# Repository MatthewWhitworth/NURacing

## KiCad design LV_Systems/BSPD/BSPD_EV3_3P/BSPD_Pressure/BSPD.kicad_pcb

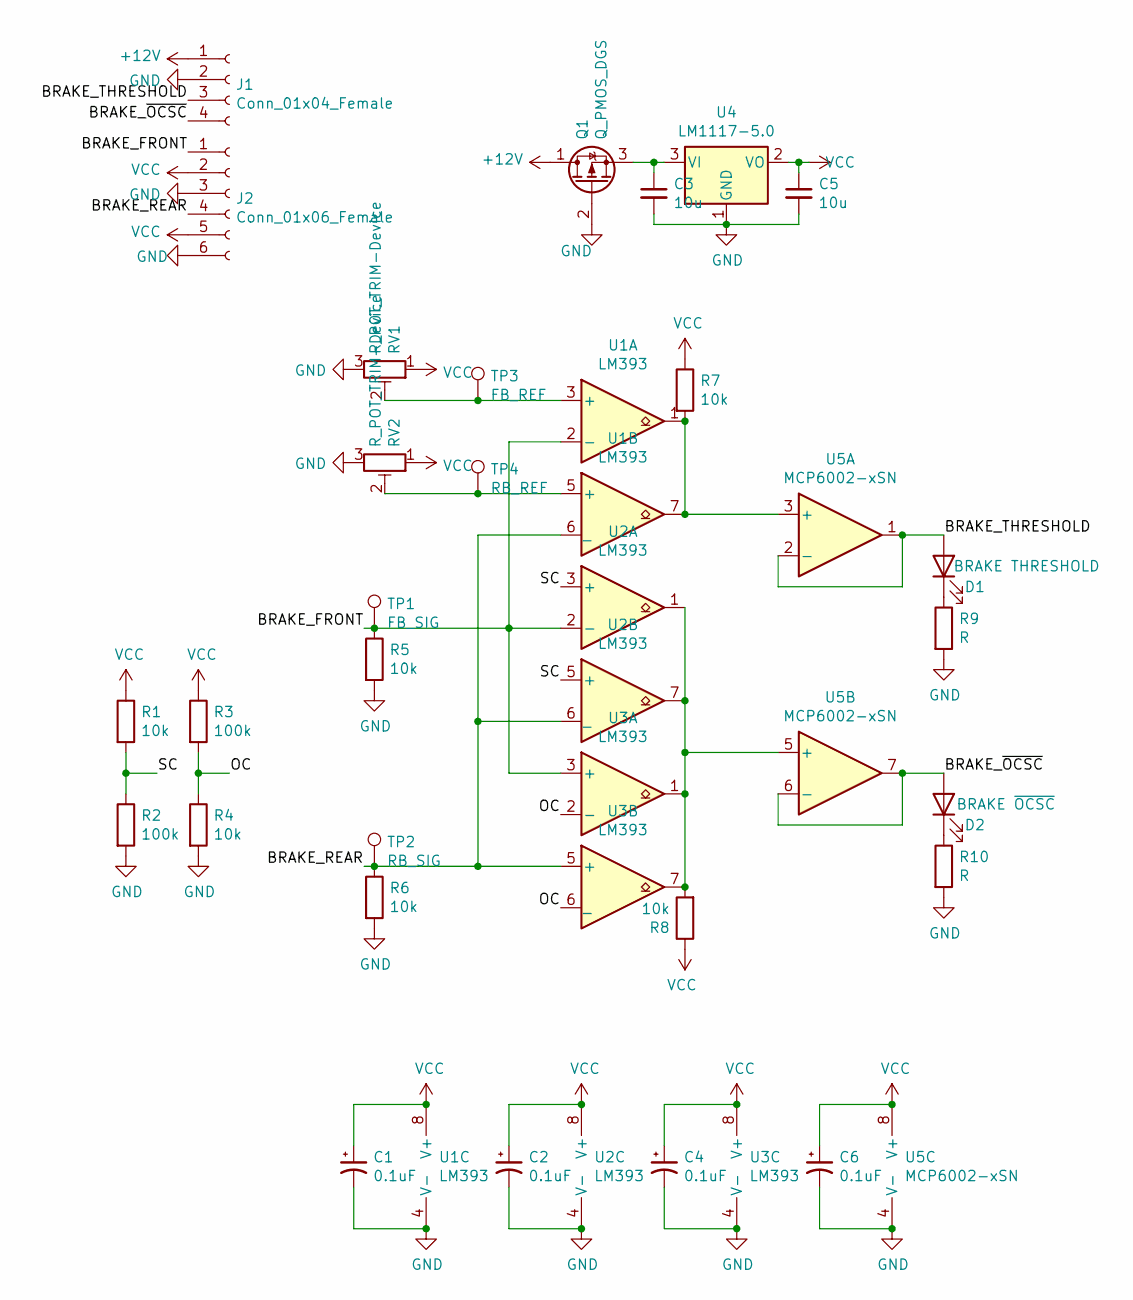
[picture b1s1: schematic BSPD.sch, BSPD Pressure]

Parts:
C1, C2, C4, C6: 0.1uF; C_0805_2012Metric
C3, C5: 10u; C_0805_2012Metric
D1: BRAKE THRESHOLD; LED_0805_2012Metric
D2: BRAKE ~OCSC; LED_0805_2012Metric
J1: Conn_01x04_Female; Molex_Micro-Fit_3.0_43045-0412_2x02_P3.00mm_Vertical
J2: Conn_01x06_Female; Molex_Micro-Fit_3.0_43045-0612_2x03_P3.00mm_Vertical
Q1: Q_PMOS_DGS; SOT-23
R1, R4, R5, R6, R7, R8: 10k; R_1206_3216Metric
R2, R3: 100k; R_1206_3216Metric
R9, R10: R; R_1206_3216Metric
RV1, RV2: R_POT_TRIM-Device; Potentiometer_Bourns_3296Y_Vertical
TP1: FB_SIG; TestPoint_Loop_D1.80mm_Drill1.0mm_Beaded
TP2: RB_SIG; TestPoint_Loop_D1.80mm_Drill1.0mm_Beaded
TP3: FB_REF; TestPoint_Loop_D1.80mm_Drill1.0mm_Beaded
TP4: RB_REF; TestPoint_Loop_D1.80mm_Drill1.0mm_Beaded
U1, U2, U3: LM393; SOIC-8_3.9x4.9mm_P1.27mm
U4: LM1117-5.0; SOT-223-3_TabPin2
U5: MCP6002-xSN; SOIC-8_3.9x4.9mm_P1.27mm

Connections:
+12V: J1.1, Q1.1 (D)
/BRAKE_FRONT: J2.1, R5.1, TP1.1, U1.2 (-), U2.2 (-), U3.3 (+)
/BRAKE_REAR: J2.4, R6.1, TP2.1, U1.6 (_), U2.6 (_), U3.5 (+)
/BRAKE_THRESHOLD: D1.2 (A), J1.3, U5.1, U5.2 (-)
/BRAKE_~OCSC: D2.2 (A), J1.4, U5.6 (-), U5.7
/OC: R3.2, R4.1, U3.2 (-), U3.6 (_)
/SC: R1.2, R2.1, U2.3 (+), U2.5 (+)
GND: C1.2, C2.2, C3.2, C4.2, C5.2, C6.2, J1.2, J2.3, J2.6, Q1.2 (G), R2.2, R4.2, R5.2, R6.2, R9.2, R10.2, RV1.3, RV2.3, U1.4 (V-), U2.4 (V-), U3.4 (V-), U4.1 (GND), U5.4 (V-)
unnamed: C3.1, Q1.3 (S), U4.3 (VI)
unnamed: D1.1 (K), R9.1
unnamed: D2.1 (K), R10.1
unnamed: R7.2, U1.1, U1.7, U5.3 (+)
unnamed: R8.2, U2.1, U2.7, U3.1, U3.7, U5.5 (+)
unnamed: RV1.2, TP3.1, U1.3 (+)
unnamed: RV2.2, TP4.1, U1.5 (+)
VCC: C1.1, C2.1, C4.1, C5.1, C6.1, J2.2, J2.5, R1.1, R3.1, R7.1, R8.1, RV1.1, RV2.1, U1.8 (V+), U2.8 (V+), U3.8 (V+), U4.2 (VO), U5.8 (V+)

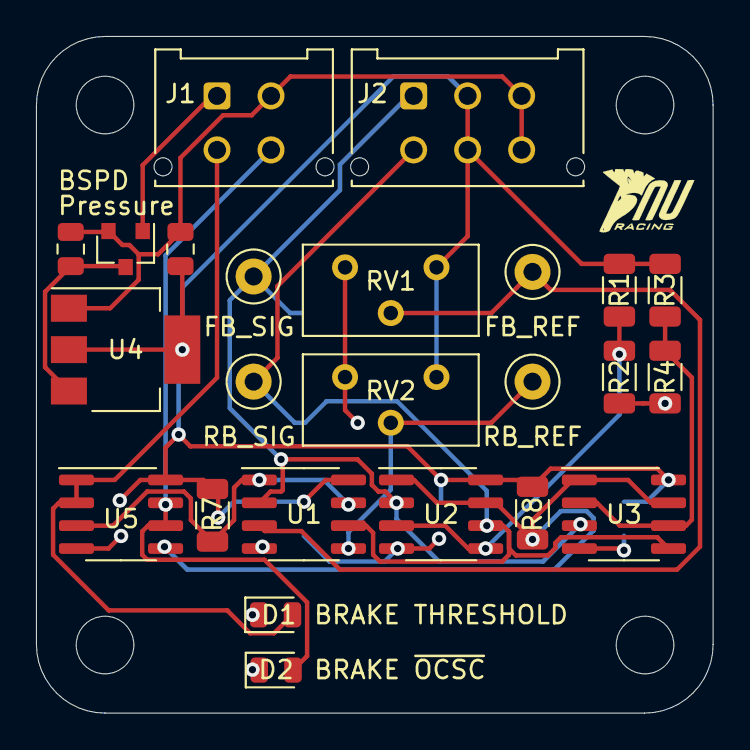
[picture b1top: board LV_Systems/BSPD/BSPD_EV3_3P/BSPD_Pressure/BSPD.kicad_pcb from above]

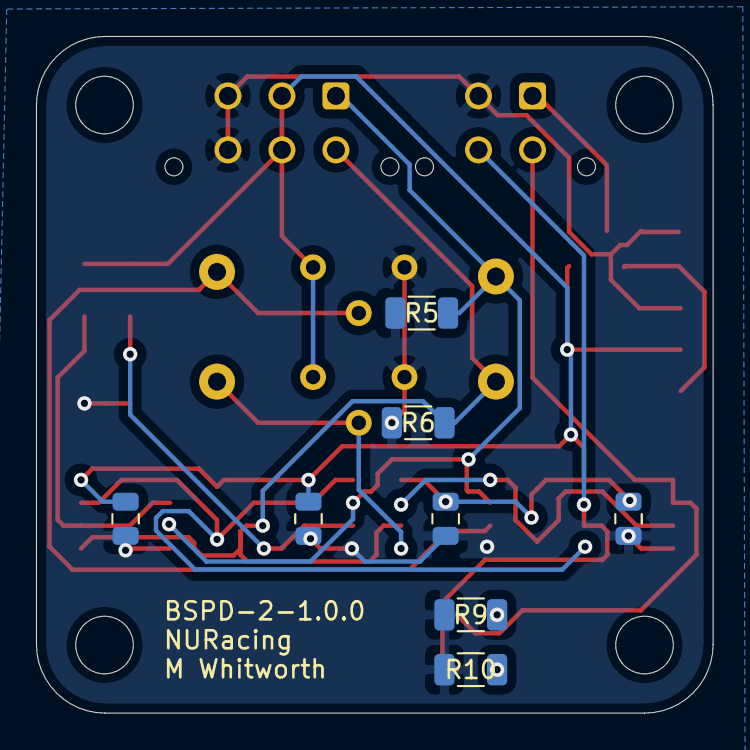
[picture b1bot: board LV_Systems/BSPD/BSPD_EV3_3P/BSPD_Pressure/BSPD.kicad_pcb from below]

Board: 2 copper layers, 37.6 x 37.6 mm, 32 parts (8 on the bottom side), 16 nets.

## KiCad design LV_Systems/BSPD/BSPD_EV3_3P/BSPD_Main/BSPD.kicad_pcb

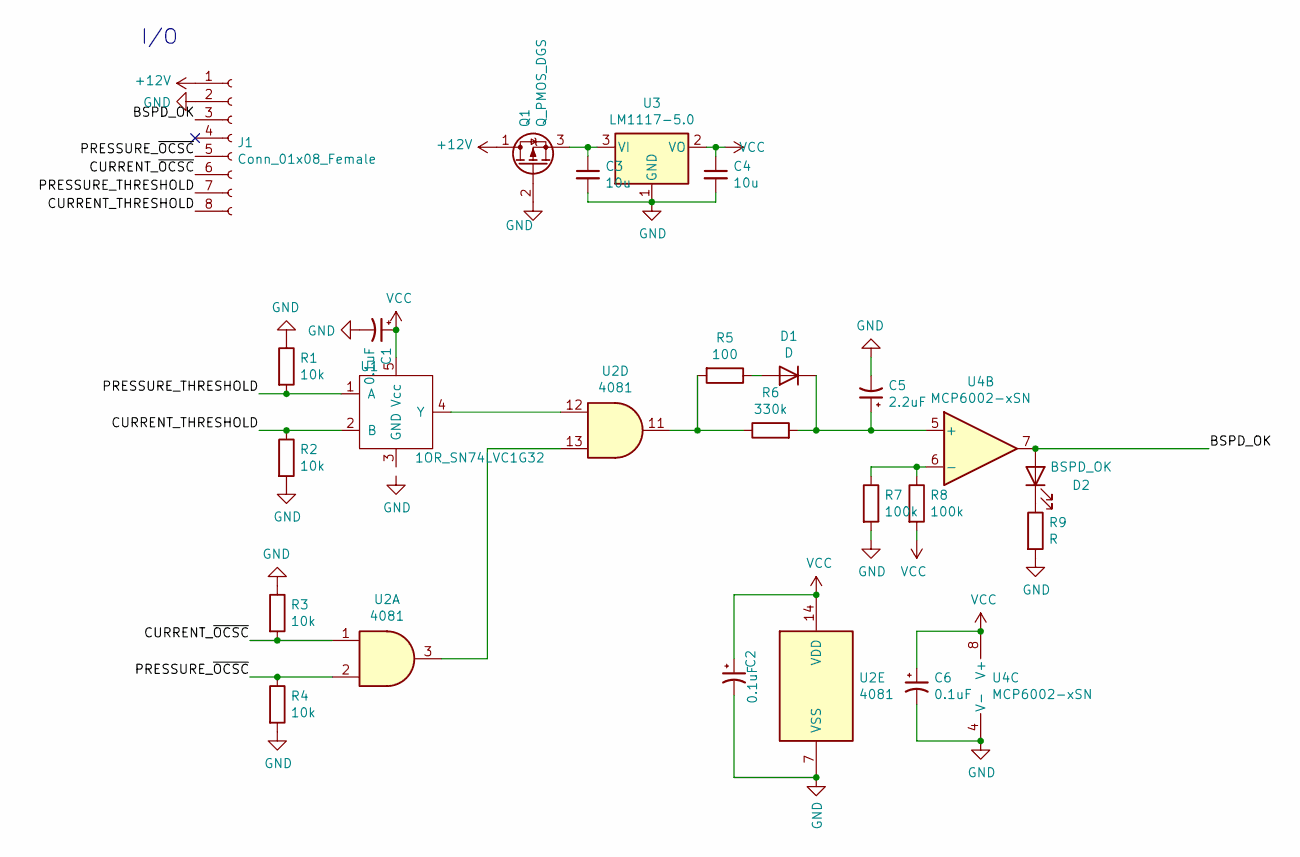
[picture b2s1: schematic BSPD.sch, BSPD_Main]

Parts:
C1, C2, C6: 0.1uF; C_0805_2012Metric
C3, C4: 10u; C_0805_2012Metric
C5: 2.2uF; C_0805_2012Metric
D1: D; D_SMA_Handsoldering
D2: BSPD_OK; LED_0805_2012Metric
J1: Conn_01x08_Female; Molex_Micro-Fit_3.0_43045-0812_2x04_P3.00mm_Vertical
Q1: Q_PMOS_DGS; SOT-23
R1, R2, R3, R4: 10k; R_1206_3216Metric
R5: 100; R_1206_3216Metric
R6: 330k; R_1206_3216Metric
R7, R8: 100k; R_1206_3216Metric
R9: R; R_1206_3216Metric
U1: 1OR_SN74LVC1G32; SOT-23-5_HandSoldering
U2: 4081; SOIC-14_3.9x8.7mm_P1.27mm
U3: LM1117-5.0; SOT-223-3_TabPin2
U4: MCP6002-xSN; SOIC-8_3.9x4.9mm_P1.27mm

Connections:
+12V: J1.1, Q1.1 (D)
/BSPD_OK: D2.2 (A), J1.3, U4.7
/CURRENT_THRESHOLD: J1.8, R2.1, U1.2 (B)
/CURRENT_~OCSC: J1.6, R3.2, U2.1
/PRESSURE_THRESHOLD: J1.7, R1.2, U1.1 (A)
/PRESSURE_~OCSC: J1.5, R4.1, U2.2
GND: C1.2, C2.2, C3.2, C4.2, C5.2, C6.2, J1.2, Q1.2 (G), R1.1, R2.2, R3.1, R4.2, R7.2, R9.2, U2.7 (VSS), U3.1 (GND), U4.4 (V-)
unnamed: C3.1, Q1.3 (S), U3.3 (VI)
unnamed: C5.1, D1.1 (K), R6.2, U4.5 (+)
unnamed: D1.2 (A), R5.1
unnamed: D2.1 (K), R9.1
unnamed: R5.2, R6.1, U2.11
unnamed: R7.1, R8.1, U4.6 (-)
unnamed: U1.4 (Y), U2.12
unnamed: U2.3, U2.13
VCC: C1.1, C2.1, C4.1, C6.1, R8.2, U1.5 (Vcc), U2.14 (VDD), U3.2 (VO), U4.8 (V+)

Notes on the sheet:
I/O

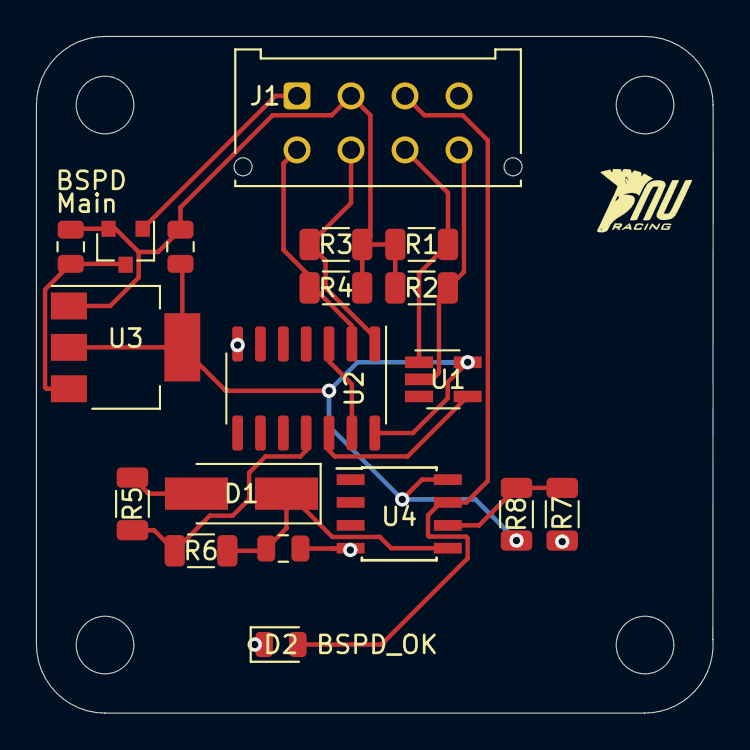
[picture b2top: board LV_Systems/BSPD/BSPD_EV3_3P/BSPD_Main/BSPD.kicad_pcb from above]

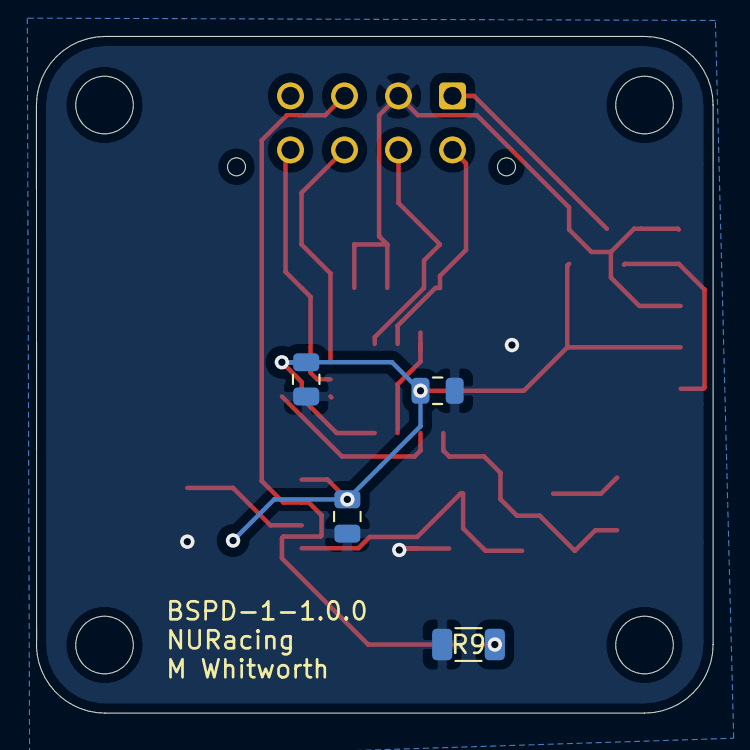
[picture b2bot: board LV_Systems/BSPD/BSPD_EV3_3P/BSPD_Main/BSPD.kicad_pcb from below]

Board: 2 copper layers, 37.6 x 37.6 mm, 23 parts (4 on the bottom side), 16 nets.

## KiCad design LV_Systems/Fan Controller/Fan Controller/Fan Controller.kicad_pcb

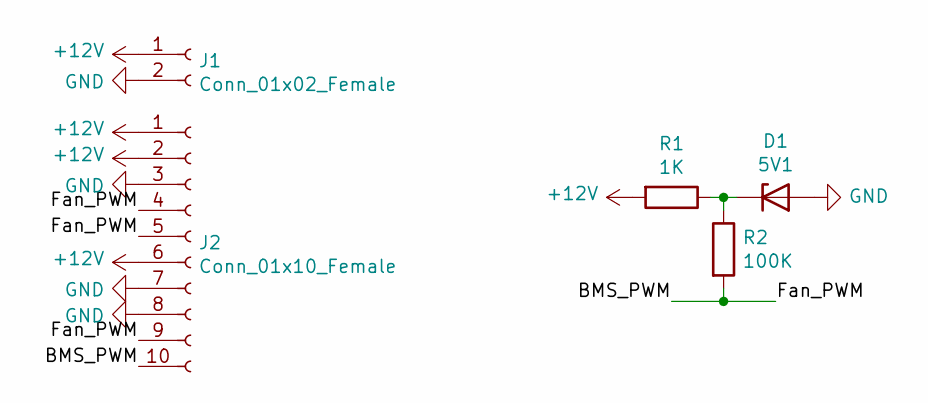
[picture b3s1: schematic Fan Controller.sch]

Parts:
D1: 5V1; SOT-23
J1: Conn_01x02_Female; Molex_Mini-Fit_Sr_42819-22XX_1x02_P10.00mm_Vertical
J2: Conn_01x10_Female; Molex_Micro-Fit_3.0_43045-1000_2x05_P3.00mm_Horizontal
R1: 1K; R_1206_3216Metric
R2: 100K; R_1206_3216Metric

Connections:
+12V: J1.1, J2.1, J2.2, J2.6, R1.2
/BMS_PWM: J2.4, J2.5, J2.9, J2.10, R2.2
GND: D1.2 (A), J1.2, J2.3, J2.7, J2.8
unnamed: D1.1 (K), R1.1, R2.1

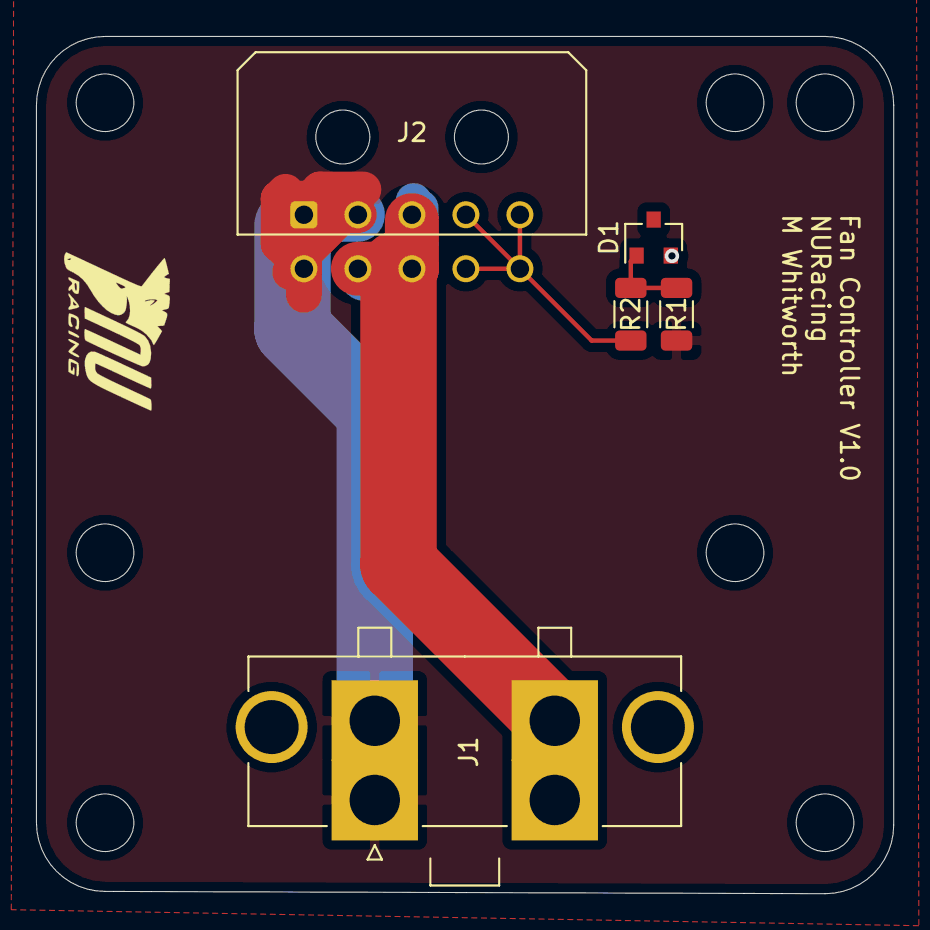
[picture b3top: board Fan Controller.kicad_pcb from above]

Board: 2 copper layers, 47.6 x 47.6 mm, 5 parts (0 on the bottom side), 4 nets.

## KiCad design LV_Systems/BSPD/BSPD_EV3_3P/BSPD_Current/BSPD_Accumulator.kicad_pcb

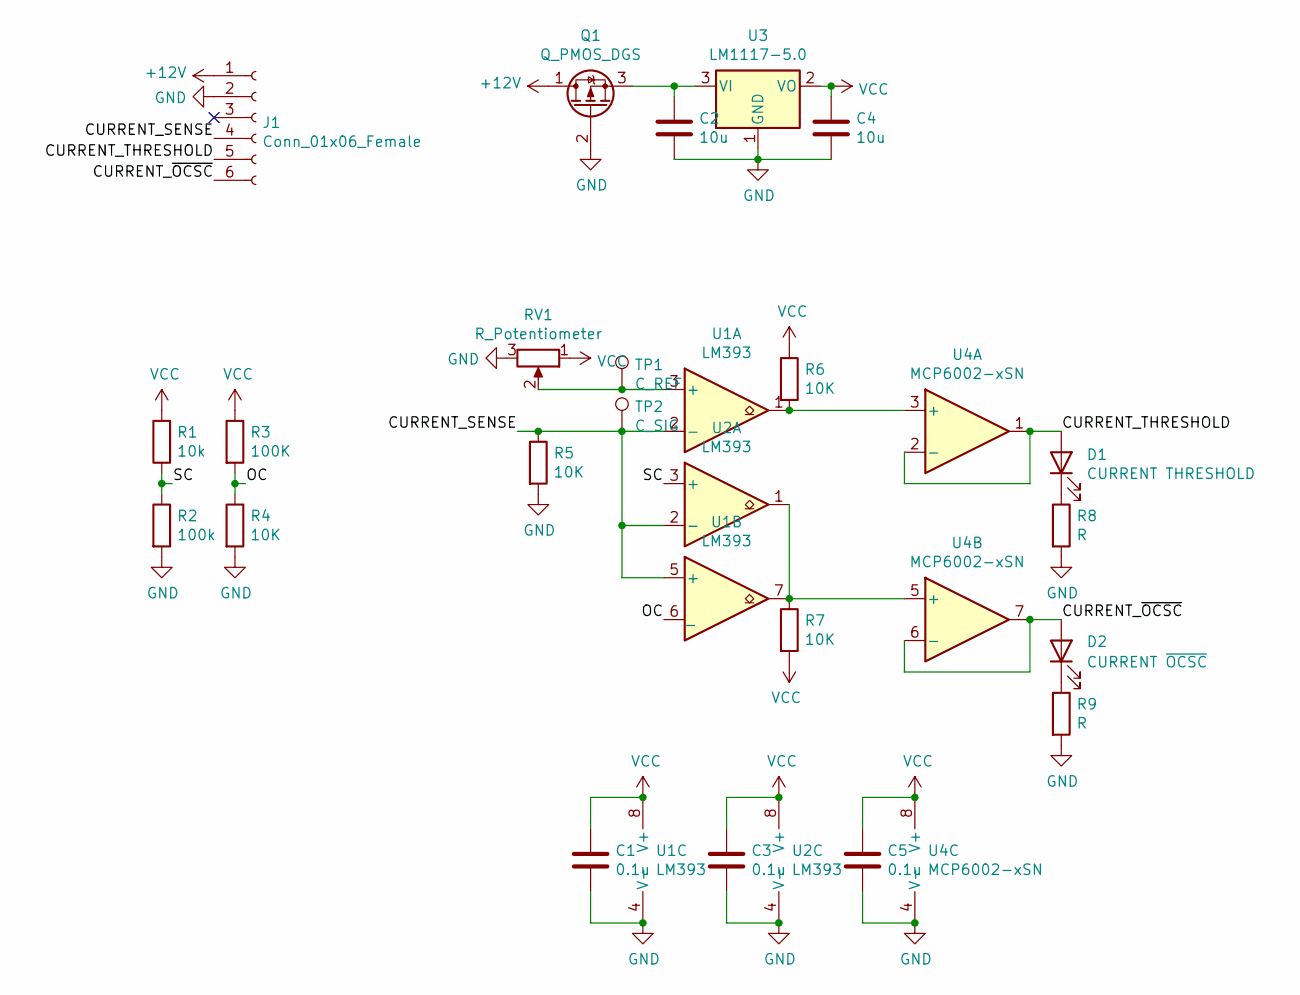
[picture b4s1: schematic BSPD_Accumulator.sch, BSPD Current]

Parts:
C1, C3, C5: 0.1u; C_0805_2012Metric
C2, C4: 10u; C_0805_2012Metric
D1: CURRENT THRESHOLD; LED_0805_2012Metric
D2: CURRENT ~OCSC; LED_0805_2012Metric
J1: Conn_01x06_Female; Molex_Micro-Fit_3.0_43045-0612_2x03_P3.00mm_Vertical
Q1: Q_PMOS_DGS; SOT-23
R1: 10k; R_1206_3216Metric
R2: 100k; R_1206_3216Metric
R3: 100K; R_1206_3216Metric
R4, R5, R6, R7: 10K; R_1206_3216Metric
R8, R9: R; R_1206_3216Metric
RV1: R_Potentiometer; Potentiometer_Bourns_3296Y_Vertical
TP1: C_REF; TestPoint_Loop_D1.80mm_Drill1.0mm_Beaded
TP2: C_SIG; TestPoint_Loop_D1.80mm_Drill1.0mm_Beaded
U1, U2: LM393; SOIC-8_3.9x4.9mm_P1.27mm
U3: LM1117-5.0; SOT-223-3_TabPin2
U4: MCP6002-xSN; SOIC-8_3.9x4.9mm_P1.27mm

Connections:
+12V: J1.1, Q1.1 (D)
/CURRENT_SENSE: J1.4, R5.1, TP2.1, U1.2 (-), U1.5 (+), U2.2 (-)
/CURRENT_THRESHOLD: D1.2 (A), J1.5, U4.1, U4.2 (-)
/CURRENT_~OCSC: D2.2 (A), J1.6, U4.6 (-), U4.7
/OC: R3.2, R4.1, U1.6 (_)
/SC: R1.1, R2.1, U2.3 (+)
GND: C1.2, C2.2, C3.2, C4.2, C5.2, J1.2, Q1.2 (G), R2.2, R4.2, R5.2, R8.2, R9.2, RV1.3, U1.4 (V-), U2.4 (V-), U3.1 (GND), U4.4 (V-)
unnamed: C2.1, Q1.3 (S), U3.3 (VI)
unnamed: D1.1 (K), R8.1
unnamed: D2.1 (K), R9.1
unnamed: R6.2, U1.1, U4.3 (+)
unnamed: R7.1, U1.7, U2.1, U4.5 (+)
unnamed: RV1.2, TP1.1, U1.3 (+)
VCC: C1.1, C3.1, C4.1, C5.1, R1.2, R3.1, R6.1, R7.2, RV1.1, U1.8 (V+), U2.8 (V+), U3.2 (VO), U4.8 (V+)

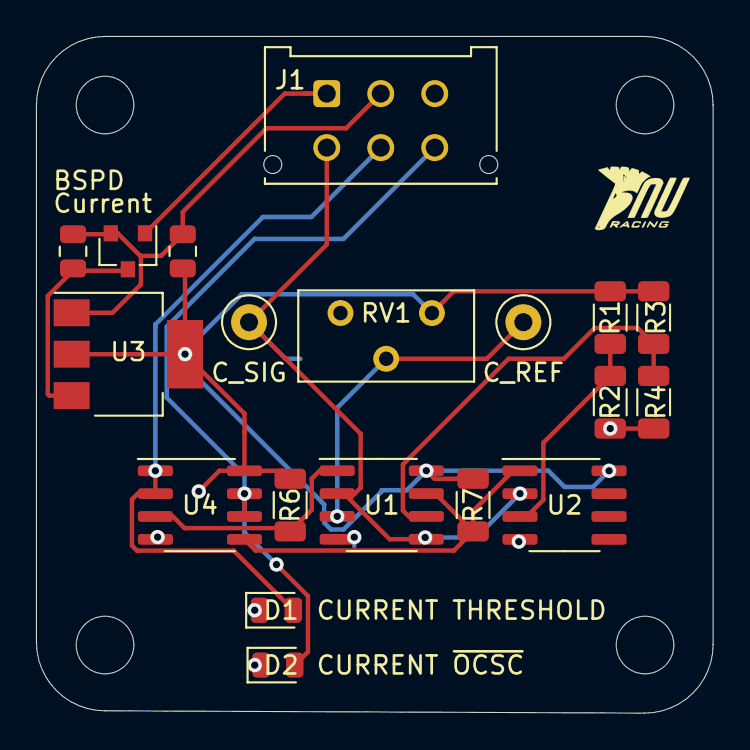
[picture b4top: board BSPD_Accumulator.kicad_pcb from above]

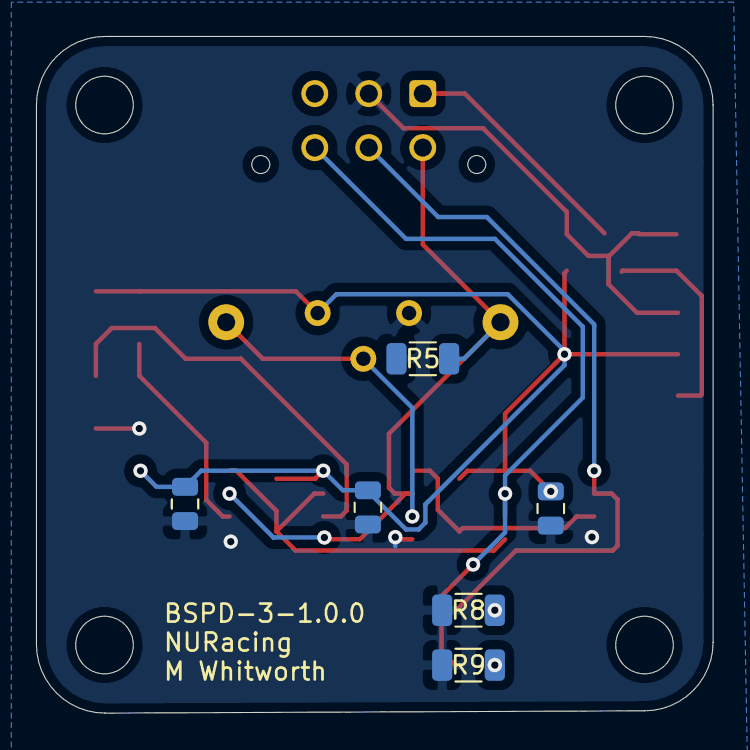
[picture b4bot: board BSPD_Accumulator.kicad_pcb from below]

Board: 2 copper layers, 37.6 x 37.6 mm, 25 parts (6 on the bottom side), 14 nets.

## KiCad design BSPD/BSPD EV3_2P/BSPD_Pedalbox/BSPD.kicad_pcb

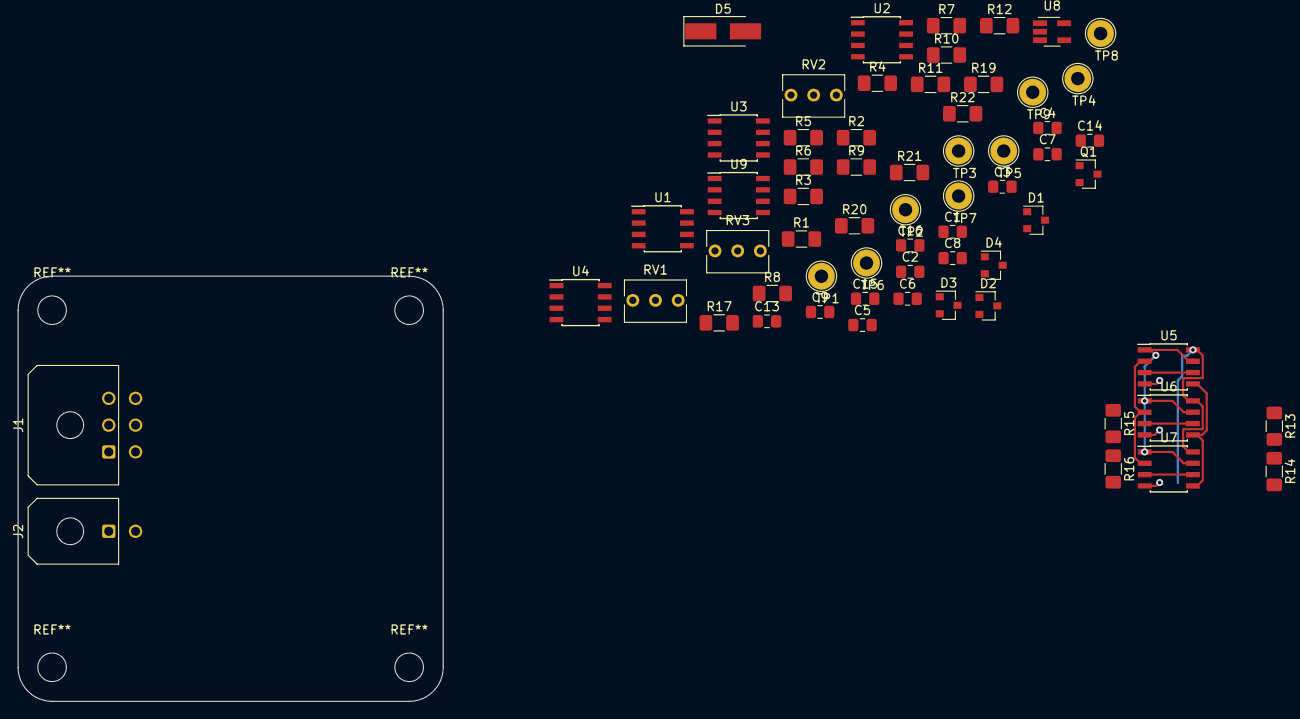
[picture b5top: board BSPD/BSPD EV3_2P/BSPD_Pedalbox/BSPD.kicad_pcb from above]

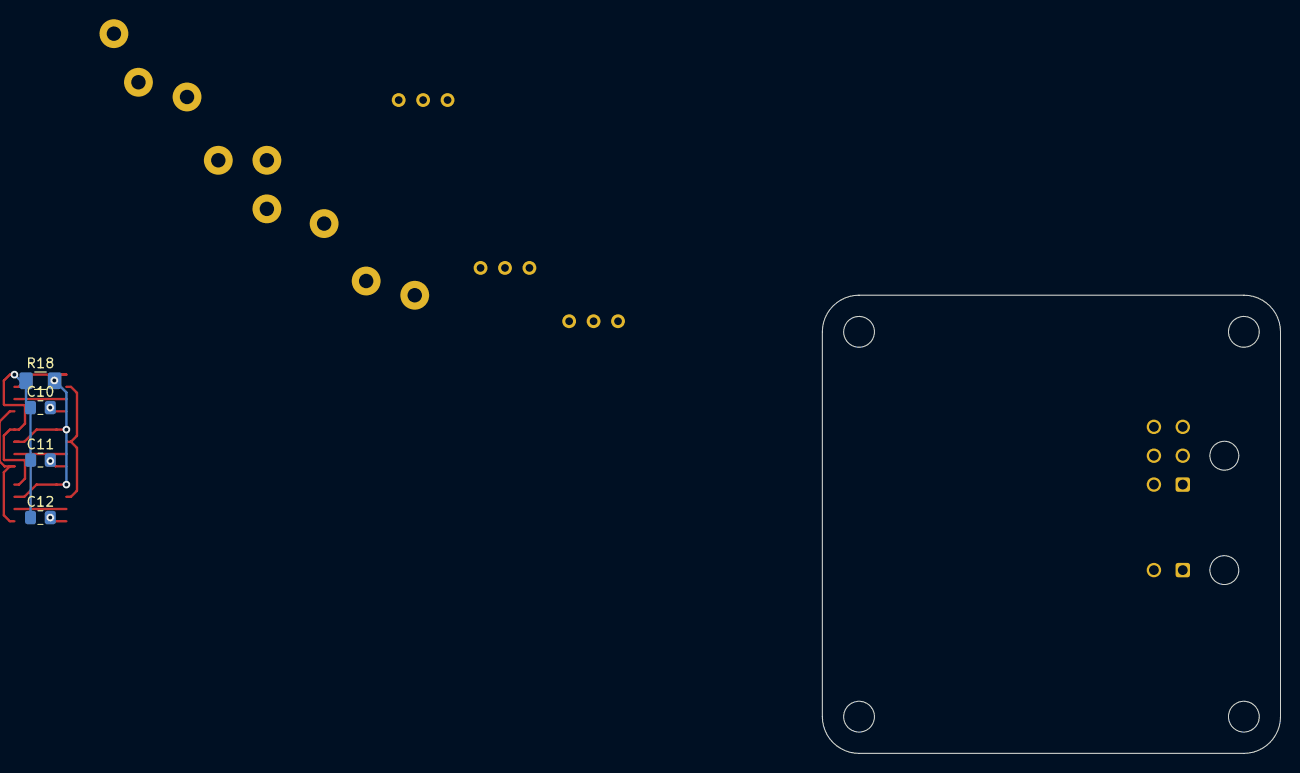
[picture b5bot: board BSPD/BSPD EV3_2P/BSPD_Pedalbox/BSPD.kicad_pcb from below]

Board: 2 copper layers, 47.6 x 47.6 mm, 67 parts (4 on the bottom side), 29 nets.

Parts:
C1, C2, C3: CP1_Small; C_0805_2012Metric_Pad1.15x1.40mm_HandSolder
C4, C5, C8: 0.1u; C_0805_2012Metric_Pad1.15x1.40mm_HandSolder
C6, C7, C9, C10, C11, C12, C13, C14, C15: 0.1uF; C_0805_2012Metric_Pad1.15x1.40mm_HandSolder
C16: 2.2uF; C_0805_2012Metric_Pad1.15x1.40mm_HandSolder
D1, D2, D3: D_Zener_Small; SOT-23
D4: D_Zener; SOT-23
D5: D; D_SMA_Handsoldering
J1: Conn_01x06_Female; Molex_Micro-Fit_3.0_43045-0600_2x03_P3.00mm_Horizontal
J2: Conn_01x02_Female; Molex_Micro-Fit_3.0_43045-0200_2x01_P3.00mm_Horizontal
Q1: Q_PMOS_DGS; SOT-23
R1, R2, R3, R4, R5, R6, R7, R8, R9, R12: R; R_1206_3216Metric_Pad1.42x1.75mm_HandSolder
R10, R11, R13, R16, R17, R18: 10k; R_1206_3216Metric_Pad1.42x1.75mm_HandSolder
R14, R15, R21, R22: 100k; R_1206_3216Metric_Pad1.42x1.75mm_HandSolder
R19: 100; R_1206_3216Metric_Pad1.42x1.75mm_HandSolder
R20: 330k; R_1206_3216Metric_Pad1.42x1.75mm_HandSolder
RV1, RV2, RV3: 10k; Potentiometer_Bourns_3266Y_Vertical
TP1, TP2, TP5: Ref; TestPoint_Loop_D2.54mm_Drill1.5mm_Beaded
TP3, TP4, TP6: Sig; TestPoint_Loop_D2.54mm_Drill1.5mm_Beaded
TP7: BrkFrnt; TestPoint_Loop_D2.54mm_Drill1.5mm_Beaded
TP8: BrkRear; TestPoint_Loop_D2.54mm_Drill1.5mm_Beaded
TP9: Current; TestPoint_Loop_D2.54mm_Drill1.5mm_Beaded
U1, U2, U3: LM311; SOIC-8_3.9x4.9mm_P1.27mm
U4: 74AUC2G08; SOIC-8_3.9x4.9mm_P1.27mm
U5, U6, U7: LM393; SOIC-8_3.9x4.9mm_P1.27mm
U8: 1OR_SN74LVC1G32; SOT-23-5_HandSoldering
U9: MCP6002-xSN; SOIC-8_3.9x4.9mm_P1.27mm

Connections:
+5V: J2.1, Q1.1
/BRK_FRNT: R8.1, R10.2, TP7.1, U1.7, U4.1
/BRK_REAR: R9.1, R11.1, TP8.1, U2.7, U4.2
/BRK_SIG: U4.7, U8.2
/Brk_Frnt_Inp: C1.1, C4.2, D1.1, R1.1, R4.1, TP3.1, U1.3, U6.3, U6.6
/Brk_Rear_Inp: C2.1, C5.2, D2.1, R2.1, R5.1, TP4.1, U2.3, U7.3, U7.6
/CRNT_SIG: R12.1, R17.2, TP9.1, U3.7, U8.1
/Crnt_Sig_Inp: C3.1, C8.2, D3.1, R3.1, R6.1, TP6.1, U3.3, U5.3, U5.6
/OC: R15.2, R16.1, U5.2, U6.2, U7.2
/Plausibility: U4.5, U8.4
/SC: R13.2, R14.1, U5.5, U6.5, U7.5
/~FLT_SIG: R19.2, R20.1, U4.3
/~OCSC: R18.2, U4.6, U5.1, U5.7, U6.1, U6.7, U7.1, U7.7
BSPD_Sig: J1.1, U9.1
GND: C1.2, C2.2, C3.2, C6.2, C7.2, C9.2, C10.2, C11.2, C12.2, C13.2, C14.2, C15.2, C16.2, D1.2, D2.2, D3.2, J1.5, J2.2, R4.2, R5.2, R6.2, R7.2, R14.2, R16.2, R21.2, RV1.3, RV2.3, RV3.3, U1.1, U1.4, U2.1, U2.4, U3.1, U3.4, U4.4, U5.4, U6.4, U7.4, U8.3, U9.4, U9.6
unnamed: C4.1, R8.2, RV1.2, TP1.1, U1.2
unnamed: C5.1, R9.2, RV2.2, TP2.1, U2.2
unnamed: C8.1, R12.2, RV3.2, TP5.1, U3.2
unnamed: C16.1, D5.1, R20.2, U9.3
unnamed: D4.2, Q1.2, R7.1
unnamed: D5.2, R19.1
unnamed: J1.2, R3.2
unnamed: J1.3, R2.2
unnamed: J1.4, R1.2
unnamed: R21.1, R22.1, U9.2
unnamed: U1.5, U1.6
unnamed: U2.5, U2.6
unnamed: U3.5, U3.6
VCC: C6.1, C7.1, C9.1, C10.1, C11.1, C12.1, C13.1, C14.1, C15.1, D4.1, J1.6, Q1.3, R10.1, R11.2, R13.1, R15.1, R17.1, R18.1, R22.2, RV1.1, RV2.1, RV3.1, U1.8, U2.8, U3.8, U4.8, U5.8, U6.8, U7.8, U8.5, U9.5, U9.8

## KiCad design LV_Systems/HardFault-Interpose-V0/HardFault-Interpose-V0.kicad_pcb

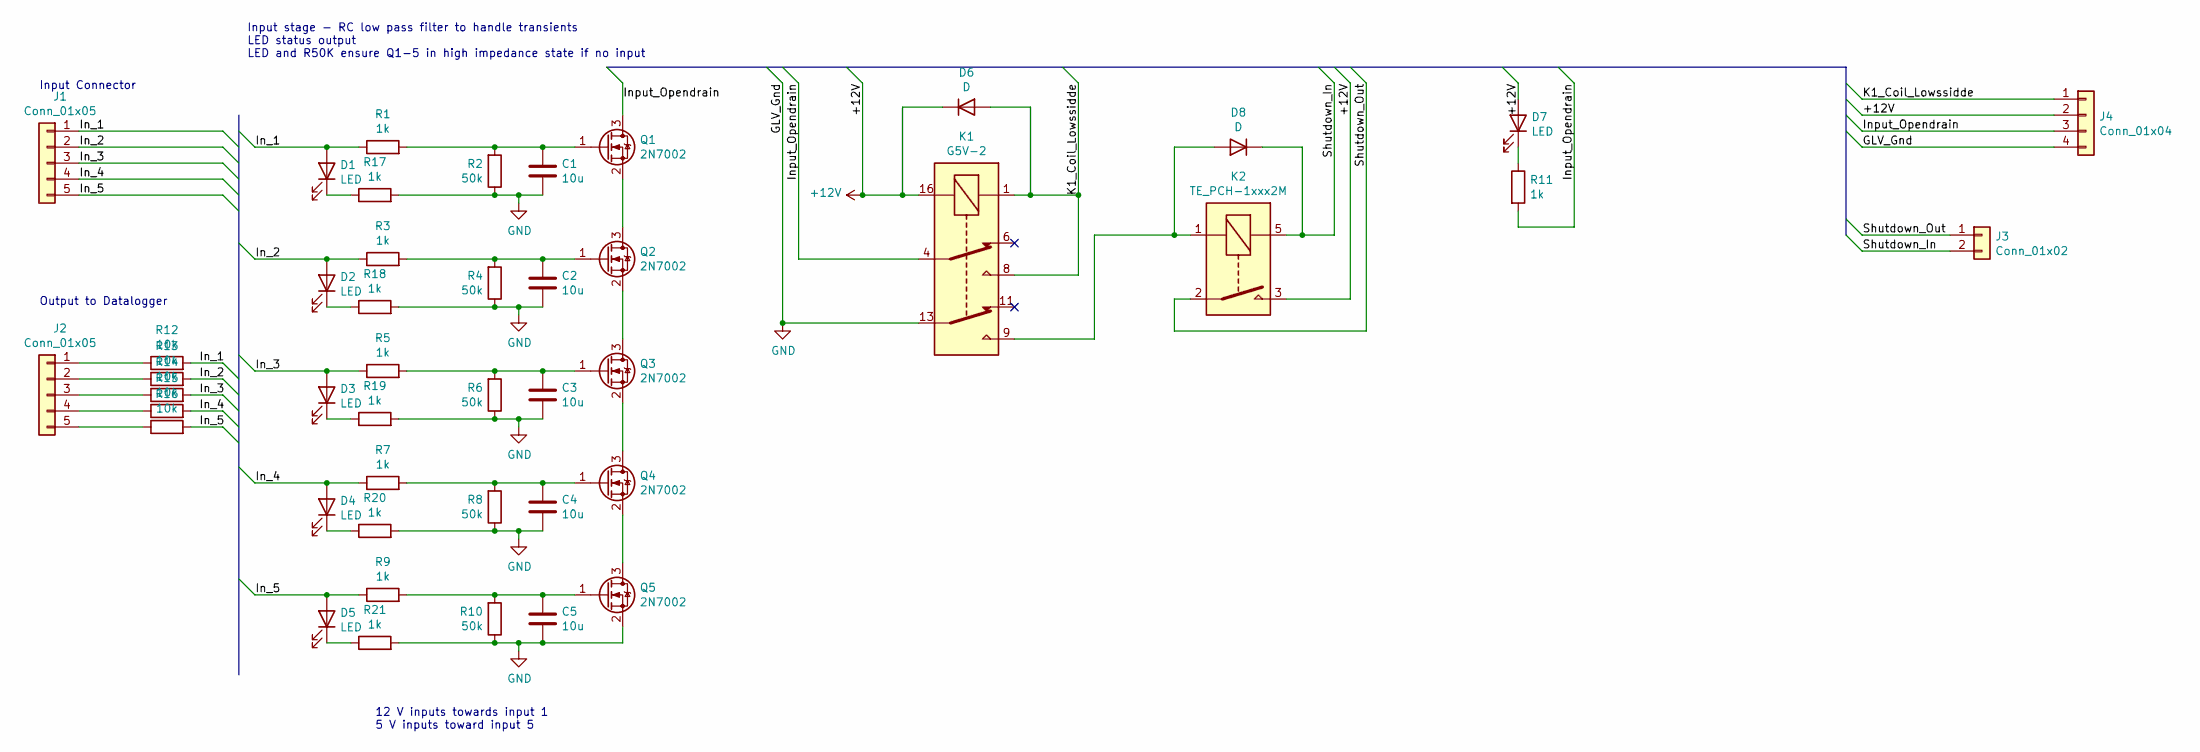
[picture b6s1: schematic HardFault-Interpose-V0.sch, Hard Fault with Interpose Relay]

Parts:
C1, C2, C3, C4, C5: 10u; C_0805_2012Metric_Pad1.15x1.40mm_HandSolder
D1, D2, D3, D4, D5, D7: LED; LED_0805_2012Metric_Castellated
D6, D8: D; D_SMA
J1, J2: Conn_01x05; Molex_Micro-Fit_3.0_43650-0515_1x05_P3.00mm_Vertical
J3: Conn_01x02; Molex-Mini-Fit-Jr-2-pin-P4.2mm-RowP4.2mm
J4: Conn_01x04; Molex-Mini-Fit-Jr-4-pin-P4.2mm-RowP4.2mm
K1: G5V-2; Relay_DPDT_Omron_G5V-2
K2: TE_PCH-1xxx2M; Relay_SPST_TE_PCH-1xxx2M
Q1, Q2, Q3, Q4, Q5: 2N7002; SOT-23
R1, R3, R5, R7, R9, R11, R17, R18, R19, R20, R21: 1k; R_1206_3216Metric_Pad1.42x1.75mm_HandSolder
R2, R4, R6, R8, R10: 50k; R_1206_3216Metric_Pad1.42x1.75mm_HandSolder
R12, R13, R14, R15, R16: 10k; R_1206_3216Metric_Pad1.42x1.75mm_HandSolder

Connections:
+12V: D6.1 (K), D7.2 (A), J4.2, K1.16, K2.3
/In_1: D1.2 (A), J1.1, R1.1, R12.2
/In_2: D2.2 (A), J1.2, R3.1, R13.2
/In_3: D3.2 (A), J1.3, R5.1, R14.2
/In_4: D4.2 (A), J1.4, R7.1, R15.2
/In_5: D5.2 (A), J1.5, R9.1, R16.2
/Input_Opendrain: J4.3, K1.4, Q1.3 (D), R11.2
/K1_Coil_Lowssidde: D6.2 (A), J4.1, K1.1, K1.8
/Shutdown_In: D8.1 (K), J3.2, K2.5
/Shutdown_Out: J3.1, K2.2
GND: C1.2, C2.2, C3.2, C4.2, C5.2, J4.4, K1.13, Q5.2 (S), R2.1, R4.1, R6.1, R8.1, R10.1, R17.2, R18.2, R19.2, R20.2, R21.2
unnamed: C1.1, Q1.1 (G), R1.2, R2.2
unnamed: C2.1, Q2.1 (G), R3.2, R4.2
unnamed: C3.1, Q3.1 (G), R5.2, R6.2
unnamed: C4.1, Q4.1 (G), R7.2, R8.2
unnamed: C5.1, Q5.1 (G), R9.2, R10.2
unnamed: D1.1 (K), R17.1
unnamed: D2.1 (K), R18.1
unnamed: D3.1 (K), R19.1
unnamed: D4.1 (K), R20.1
unnamed: D5.1 (K), R21.1
unnamed: D7.1 (K), R11.1
unnamed: D8.2 (A), K1.9, K2.1
unnamed: J2.1, R12.1
unnamed: J2.2, R13.1
unnamed: J2.3, R14.1
unnamed: J2.4, R15.1
unnamed: J2.5, R16.1
unnamed: Q1.2 (S), Q2.3 (D)
unnamed: Q2.2 (S), Q3.3 (D)
unnamed: Q3.2 (S), Q4.3 (D)
unnamed: Q4.2 (S), Q5.3 (D)

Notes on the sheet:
Input stage - RC low pass filter to handle transients LED status output LED and R50K ensure Q1-5 in high impedance state if no input
Input Connector
Output to Datalogger
12 V inputs towards input 1 5 V inputs toward input 5

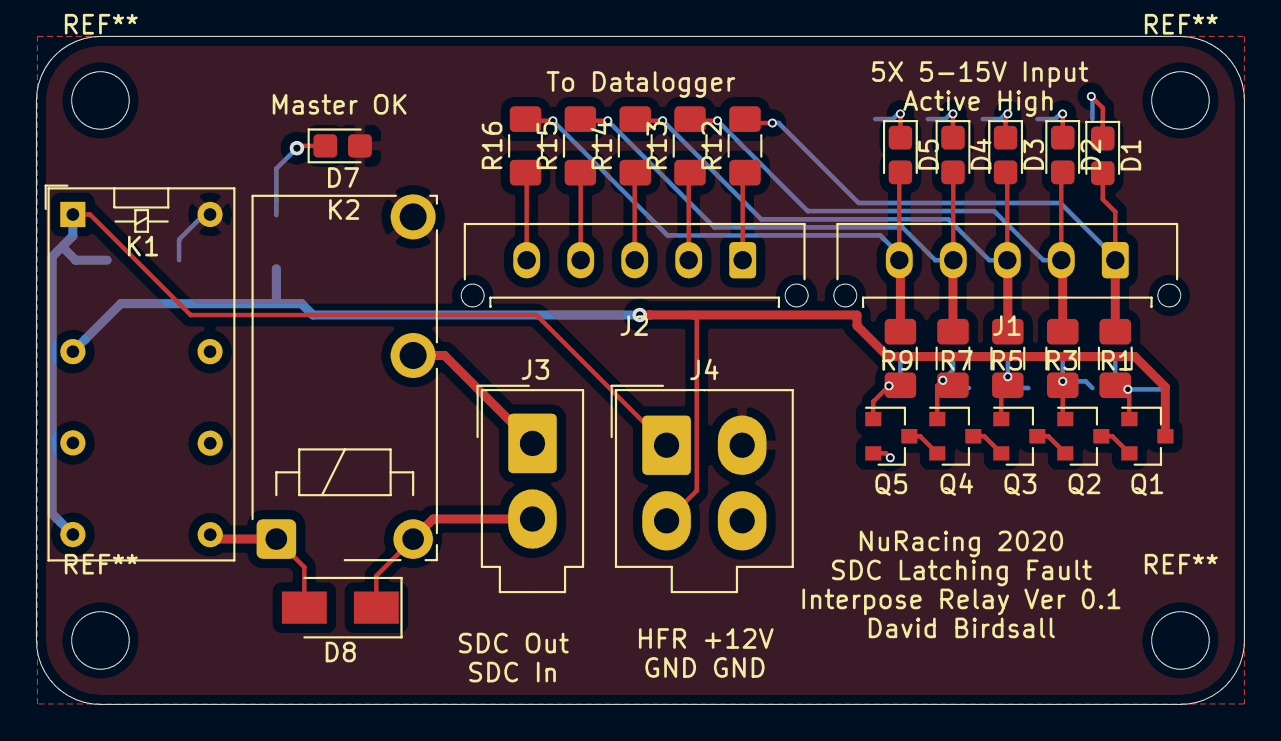
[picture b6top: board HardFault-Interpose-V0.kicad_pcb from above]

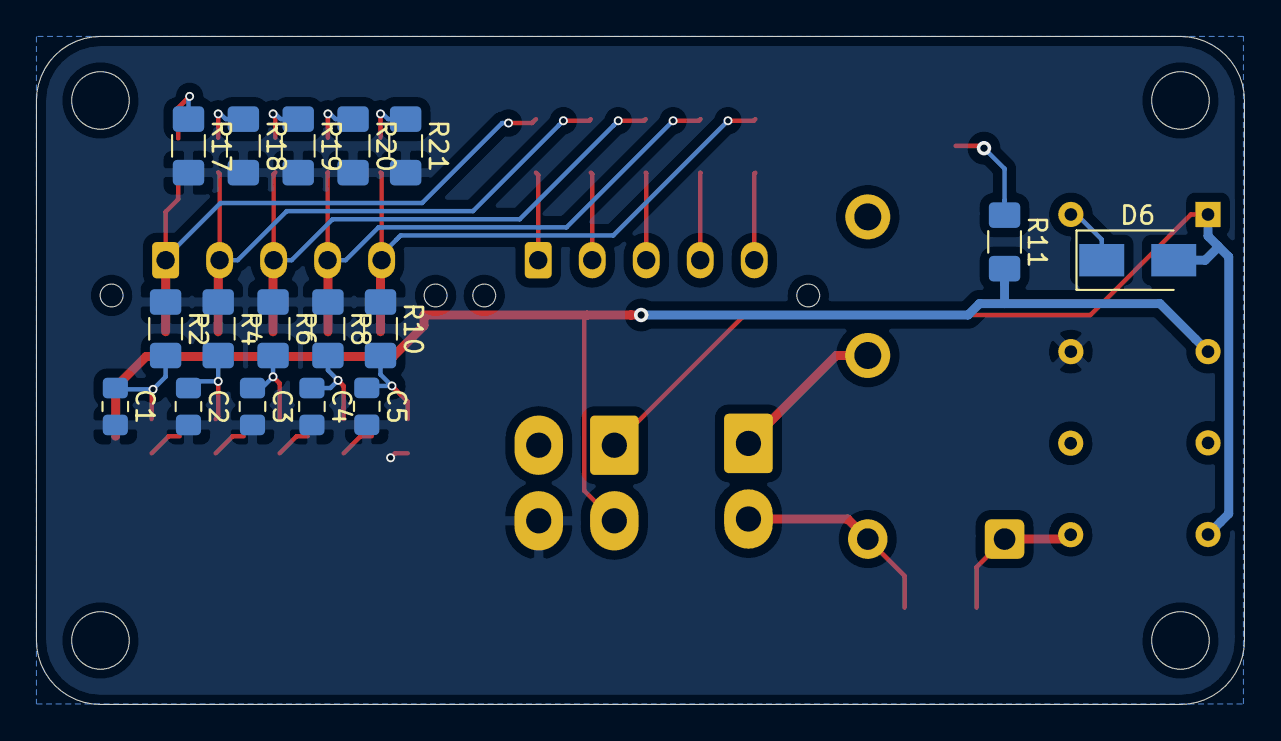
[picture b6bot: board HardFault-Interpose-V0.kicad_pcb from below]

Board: 2 copper layers, 67.1 x 37.1 mm, 45 parts (17 on the bottom side), 32 nets.

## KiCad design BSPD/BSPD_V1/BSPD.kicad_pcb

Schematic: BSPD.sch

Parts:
C1: 0.1u; C_0805_2012Metric
C2, C5: 0.1u; C_0805_2012Metric_Pad1.15x1.40mm_HandSolder
C3, C4, C6, C7, C9, C11, C13, C14, C15, C16, C17: 0.1uF; C_0805_2012Metric_Pad1.15x1.40mm_HandSolder
C8: 1u; C_0805_2012Metric_Pad1.15x1.40mm_HandSolder
C10: 100n; C_0805_2012Metric_Pad1.15x1.40mm_HandSolder
C12: 2.2uF; C_0805_2012Metric_Pad1.15x1.40mm_HandSolder
D1, D2, D7: D; D_SMA_Handsoldering
D3, D4, D5, D6, D8: LED; D_0805_2012Metric_Pad1.15x1.40mm_HandSolder
D9: ~OCSC; D_0805_2012Metric_Pad1.15x1.40mm_HandSolder
J1: Conn_01x06_Female; Molex-Mini-Fit-Jr-6-pin-P4.2mm-RowP4.2mm
J2: Conn_01x04_Female; Molex-Mini-Fit-Jr-4-pin-P4.2mm-RowP4.2mm
J3: Conn_01x02_Female; Molex-Mini-Fit-Jr-2-pin-P4.2mm-RowP4.2mm
R1, R2, R5: R; R_1206_3216Metric_Pad1.42x1.75mm_HandSolder
R3, R4, R6, R16, R19: 10k; R_1206_3216Metric_Pad1.42x1.75mm_HandSolder
R7, R8, R9, R10, R15, R20: 3.3k; R_1206_3216Metric_Pad1.42x1.75mm_HandSolder
R11: 100; R_1206_3216Metric_Pad1.42x1.75mm_HandSolder
R12: 330k; R_1206_3216Metric_Pad1.42x1.75mm_HandSolder
R13, R14, R17, R18: 100k; R_1206_3216Metric_Pad1.42x1.75mm_HandSolder
RV1, RV2, RV3: 10k; Potentiometer_Bourns_3266Y_Vertical
TP1, TP2, TP5: Ref; TestPoint_Loop_D2.54mm_Drill1.5mm_Beaded
TP3, TP4, TP6: Sig; TestPoint_Loop_D2.54mm_Drill1.5mm_Beaded
TP7: BrkFrnt; TestPoint_Loop_D2.54mm_Drill1.5mm_Beaded
TP8: BrkRear; TestPoint_Loop_D2.54mm_Drill1.5mm_Beaded
TP9: Current; TestPoint_Loop_D2.54mm_Drill1.5mm_Beaded
TP10: GND; TestPoint_Loop_D2.54mm_Drill1.5mm_Beaded
U1, U2, U3: LM311; SOIC-8_3.9x4.9mm_P1.27mm
U4, U12: 74LS08; SOIC-14_3.9x8.7mm_P1.27mm
U5: MCP6004; SOIC-14_3.9x8.7mm_P1.27mm
U6: LM1117-5.0; SOT-223-3_TabPin2
U7: 1OR_SN74LVC1G32; SOT-23-5_HandSoldering
U8, U9, U10, U11: MCP6002-xSN; SOIC-8_3.9x4.9mm_P1.27mm

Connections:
+12V: C8.1, D1.1, D2.1, U6.3
/BRKF_~OCSC: U4.10, U12.6
/BRKR_~OCSC: U4.11, U12.2
/BRK_FRNT: R1.1, R3.2, TP7.1, U1.7, U4.2, U5.5
/BRK_REAR: R2.1, R4.1, TP8.1, U2.7, U4.1, U5.10
/BRK_SIG: U4.3, U7.2 (B)
/CS_~OCSC: U4.6, U4.9
/Plausibility: U5.12, U7.4 (Y), U12.10
/~FLT_SIG: R11.2, R12.1, U12.8
/~OCSC: R20.2, U12.3, U12.9
BSPD_Sig: D8.2, J2.1, U8.1
BrkFrnt: C1.2, J1.4, TP3.1, U1.3, U10.3, U10.6
BrkRear: C2.2, J1.1, TP4.1, U2.3, U11.3, U11.6
Current_Led: R5.1, R6.2, TP9.1, U3.7, U5.3, U7.1 (A)
Current_Sense: C5.2, J2.2, TP6.1, U3.3, U9.3, U9.6
GND: C3.2, C4.2, C6.2, C7.2, C8.2, C9.2, C10.2, C11.2, C12.2, C13.2, C14.2, C15.2, C16.2, C17.2, D3.1, D4.1, D5.1, D6.1, D9.1, J1.2, J1.5, J3.2, R13.2, R15.1, R17.2, R19.2, RV1.3, RV2.3, RV3.3, TP10.1, U1.1, U1.4, U2.1, U2.4, U3.1, U3.4, U4.7, U5.11, U6.1, U7.3 (GND), U8.4, U8.6, U9.4, U10.4, U11.4, U12.7
unnamed: C1.1, R1.2, RV1.2, TP1.1, U1.2
unnamed: C2.1, R2.2, RV2.2, TP2.1, U2.2
unnamed: C5.1, R5.2, RV3.2, TP5.1, U3.2
unnamed: C12.1, D7.1, R12.2, U8.3
unnamed: D1.2, J3.1
unnamed: D3.2, R7.1
unnamed: D4.2, R8.1
unnamed: D5.2, R9.1
unnamed: D6.2, R10.1
unnamed: D7.2, R11.1
unnamed: D8.1, R15.2
unnamed: D9.2, R20.1
unnamed: R7.2, U5.1, U5.2
unnamed: R8.2, U5.6, U5.7
unnamed: R9.2, U5.8, U5.9
unnamed: R10.2, U5.13, U5.14
unnamed: R13.1, R14.1, U8.2
unnamed: U1.5, U1.6
unnamed: U2.5, U2.6
unnamed: U3.5, U3.6
unnamed: U4.4, U9.1
unnamed: U4.5, U9.7
unnamed: U10.1, U12.4
unnamed: U10.7, U12.5
unnamed: U4.12, U11.1
unnamed: U4.13, U11.7
unnamed: U4.8, U12.1
OC: R18.2, R19.1, U9.2, U10.2, U11.2
SC: R16.2, R17.1, U9.5, U10.5, U11.5
VCC: C3.1, C4.1, C6.1, C7.1, C9.1, C10.1, C11.1, C13.1, C14.1, C15.1, C16.1, C17.1, D2.2, J1.3, J1.6, J2.4, R3.1, R4.2, R6.1, R14.2, R16.1, R18.1, RV1.1, RV2.1, RV3.1, U1.8, U2.8, U3.8, U4.14, U5.4, U6.2, U7.5 (Vcc), U8.5, U8.8, U9.8, U10.8, U11.8, U12.14

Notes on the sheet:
500ms signal delay
Output signal to HFL which latches shutdown open on bspd fault active low
Check for hard braking from either front or rear brakes active low
5 V board supply
Check for > 5kW of power draw active low
component values not final
I/O
OC and SC Detection
LED Driver
